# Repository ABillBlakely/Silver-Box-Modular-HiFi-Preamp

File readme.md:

# Silver Box Modular HiFi Preamp

> __Note: This project is still very early in development. Features, functions, and interfaces are subject to change.__

The Silver Box Modular HiFi Preamp allows a person to choose the exact inputs and outputs that a user wants to have. It is common to need to combine or switch between many different sources which all need to go to a single playback source. For instance a person may have TOSLINK optical from their TV, RCA source from a turntable, and a balanced source from a USB audio interface. With this device, all of those can be accommodated and output to one set of speakers.

The chassis provides the analog signal routing, volume control, switching and indication. It is driven by an ESP32 so that functions can be controlled over WiFi, and eventually with smart home integration.

Peripherals are modular cards that can be slotted in to any of the available channels. Peripherals can be active or passive and can function as inputs, outputs, effects, visualizations, maybe more!

The chassis provides each peripheral with:

- Audio send to summing bus, main bus audio output, and audio out from left-adjacent module.
- Global mute and per peripheral muting.
- +/- 12V, +5V, +3.3V power rails.
- An I2C data interface with interrupt capabilities.
- Automatic identification of common module types with additional configuration possible over I2C.

# Current Status

__April 25 2023 Update:__ The project is currently in the __hardware prototyping__ phase. PCB's have been produced and are being assembled. Very close to beginning testing. A minimum viable product could be functional by end of May 2023.

Design files will be updated here as progress is made.

The current schematics are available in .pdf in the __ecad__ folder:

- [ecad/motherboard.pdf](ecad/motherboard.pdf)
- [ecad/controlboard.pdf](ecad/controlboard.pdf)
- [ecad/peripheral-example-board.pdf](ecad/peripheral-example-board.pdf)
- [ecad/prototype-power-supply.pdf](ecad/prototype-power-supply.pdf)

The current 3D models/assemblies for the project are available in .step format in the __mcad__ folder:

- [mcad/silver-box-modular_assembly.step](mcad/silver-box-modular_assembly.step)
- [mcad/motherboard.step](mcad/motherboard.step)
- [mcad/controlboard.step](mcad/controlboard.step)
- [mcad/peripheral-example-board.step](mcad/peripheral-example-board.step)

The BOM for this project is evolving and changing with the project. The current state of the BOM can be viewed at 

- [Motherboard](https://octopart.com/bom-tool/XiIWqOJY)
- [Peripheral test board](https://octopart.com/bom-tool/2ID8Y56N)
- [Protype power supply](https://octopart.com/bom-tool/b4PDtAU9)

Next steps:

- [ ] Bring docs up to date with current development state.
- [ ] Setup dev environment
- [ ] Document the mcad model and explain key features.
- [ ] Organize and refine the 3d prints that will be required for the prototype.
- [ ] Put together power supply module that will be used for early development.
  	- Board should have breakouts for external lab power option
  	- MCU for development and testing of I2C, power sequencing, power monitoring
  	- Polyfuse or other protection circuit. 
- [x] Create blank/passive modules for prototyping.
- [x] Synchronize/clean the Octopart BOM with the schematic.
- [x] Final review and production of prototype PCB's.

Farther out:

- 4 layer board after hardware features and form is frozen.
- Power supply design following findings learned from prototyping efforts.
- Expand available peripheral designs, active balanced I/O. Headphone amp output, S/PDIF digital input, VU 
- Integrate with MQTT for smart home capabilities. Eventual integration with commercial smart home systems.

# Concept sketches/renders:

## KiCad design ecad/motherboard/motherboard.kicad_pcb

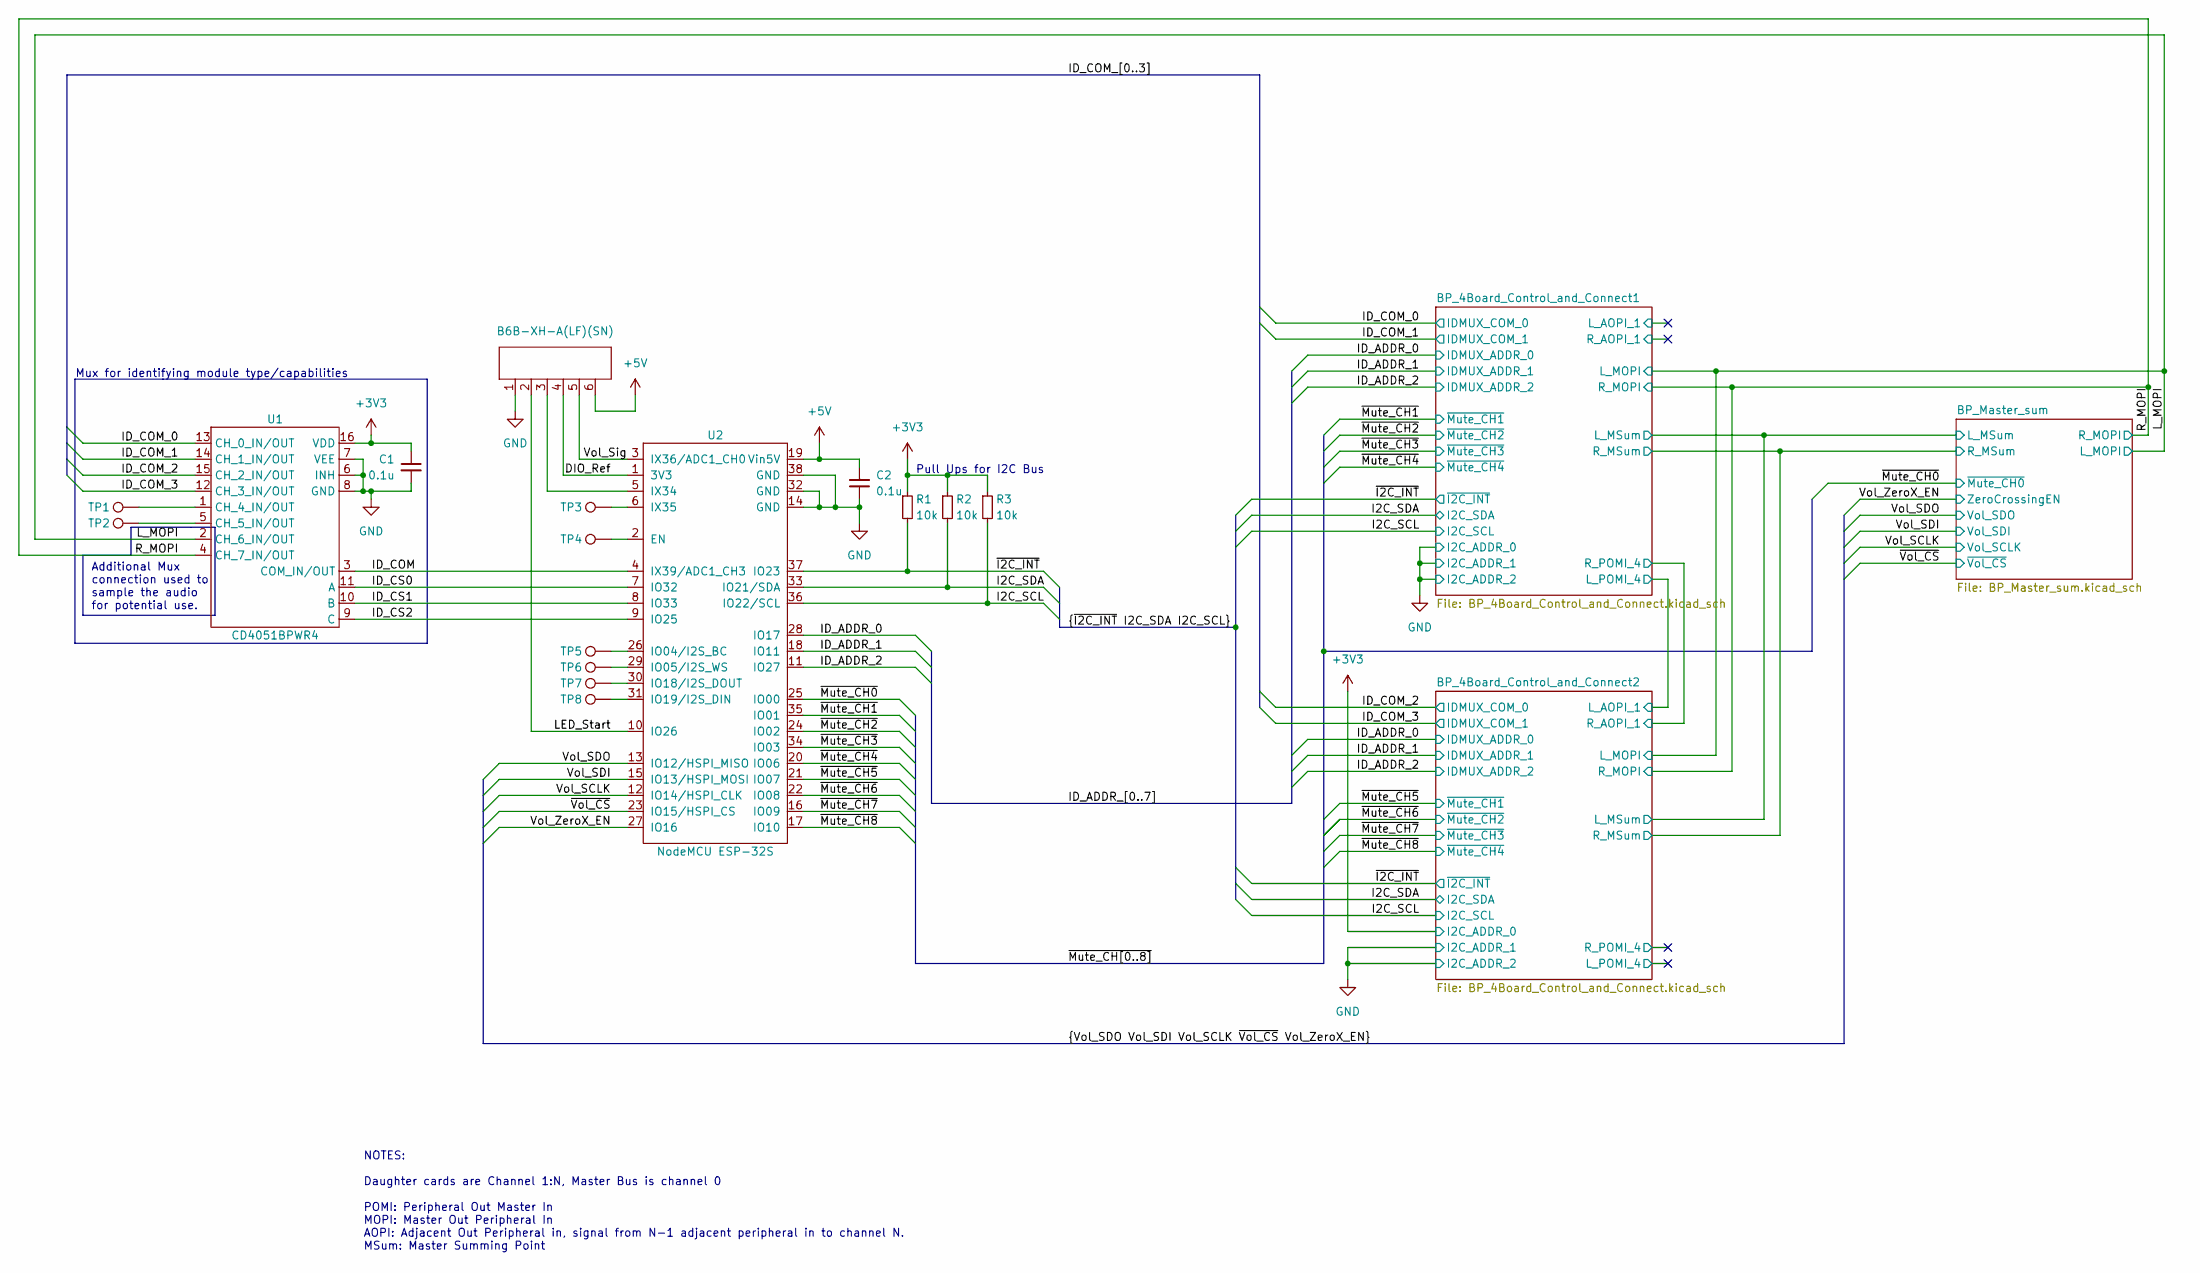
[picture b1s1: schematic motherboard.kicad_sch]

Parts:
C1, C2: 0.1u; C_0603_1608Metric_Pad1.08x0.95mm_HandSolder; MPN C0603C104M5RACTU
J1: B6B-XH-A(LF)(SN); MPN B6B-XH-A(LF)(SN)
R1, R2, R3: 10k; R_0603_1608Metric_Pad0.98x0.95mm_HandSolder; MPN RC0603JR-1010KL
TP1, TP2, TP3, TP4, TP5, TP6, TP7, TP8: TestPoint; TestPoint_Pad_D3.0mm
U1: CD4051BPWR4; CD4051BPWR; MPN CD4051BPWR
U2: NodeMCU ESP-32S

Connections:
+3V3: C1.1, R1.1, R2.1, R3.1, U1.16 (VDD); also elsewhere on the board
+5V: C2.2, J1.6, U2.19 (Vin5V); also elsewhere on the board
/DIO_Ref: J1.4, U2.1 (3V3)
/I2C_SCL: R3.2, U2.36 (IO22/SCL); also elsewhere on the board
/I2C_SDA: R2.2, U2.33 (IO21/SDA); also elsewhere on the board
/ID_ADDR_0: U2.28 (IO17); also elsewhere on the board
/ID_ADDR_1: U2.18 (IO11); also elsewhere on the board
/ID_ADDR_2: U2.11 (IO27); also elsewhere on the board
/ID_COM: U1.3 (COM_IN/OUT), U2.4 (IX39/ADC1_CH3)
/ID_COM_0: U1.13 (CH_0_IN/OUT); also elsewhere on the board
/ID_COM_1: U1.14 (CH_1_IN/OUT); also elsewhere on the board
/ID_COM_2: U1.15 (CH_2_IN/OUT); also elsewhere on the board
/ID_COM_3: U1.12 (CH_3_IN/OUT); also elsewhere on the board
/ID_CS0: U1.11 (A), U2.7 (IO32)
/ID_CS1: U1.10 (B), U2.8 (IO33)
/ID_CS2: U1.9 (C), U2.9 (IO25)
/LED_Start: J1.2, U2.10 (IO26)
/L_MOPI: U1.2 (CH_6_IN/OUT); also elsewhere on the board
/R_MOPI: U1.4 (CH_7_IN/OUT); also elsewhere on the board
/Vol_SCLK: U2.12 (IO14/HSPI_CLK); also elsewhere on the board
/Vol_SDI: U2.15 (IO13/HSPI_MOSI); also elsewhere on the board
/Vol_SDO: U2.13 (IO12/HSPI_MISO); also elsewhere on the board
/Vol_Sig: J1.5, U2.3 (IX36/ADC1_CH0)
/Vol_ZeroX_EN: U2.27 (IO16); also elsewhere on the board
/~I2C_INT: R1.2, U2.37 (IO23); also elsewhere on the board
/~Mute_CH0: U2.25 (IO00); also elsewhere on the board
/~Mute_CH1: U2.35 (IO01); also elsewhere on the board
/~Mute_CH2: U2.24 (IO02); also elsewhere on the board
/~Mute_CH3: U2.34 (IO03); also elsewhere on the board
/~Mute_CH4: U2.20 (IO06); also elsewhere on the board
/~Mute_CH5: U2.21 (IO07); also elsewhere on the board
/~Mute_CH6: U2.22 (IO08); also elsewhere on the board
/~Mute_CH7: U2.16 (IO09); also elsewhere on the board
/~Mute_CH8: U2.17 (IO10); also elsewhere on the board
/~Vol_CS: U2.23 (IO15/HSPI_CS); also elsewhere on the board
GND: C1.2, C2.1, J1.1, U1.6 (INH), U1.7 (VEE), U1.8 (GND), U2.14 (GND), U2.32 (GND), U2.38 (GND); also elsewhere on the board
unnamed: TP1.1, U1.1 (CH_4_IN/OUT)
unnamed: TP2.1, U1.5 (CH_5_IN/OUT)
unnamed: TP4.1, U2.2 (EN)
unnamed: TP5.1, U2.26 (IO04/I2S_BC)
unnamed: TP6.1, U2.29 (IO05/I2S_WS)
unnamed: TP7.1, U2.30 (IO18/I2S_DOUT)
unnamed: TP8.1, U2.31 (IO19/I2S_DIN)
unnamed: J1.3, U2.5 (IX34)
unnamed: TP3.1, U2.6 (IX35)

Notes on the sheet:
Pull Ups for I2C Bus
NOTES: Daughter cards are Channel 1:N, Master Bus is channel 0 POMI: Peripheral Out Master In MOPI: Master Out Peripheral In AOPI: Adjacent Out Peripheral in, signal from N-1 adjacent peripheral in to channel N. MSum: Master Summing Point
Mux for identifying module type/capabilities
Additional Mux connection used to sample the audio for potential use.

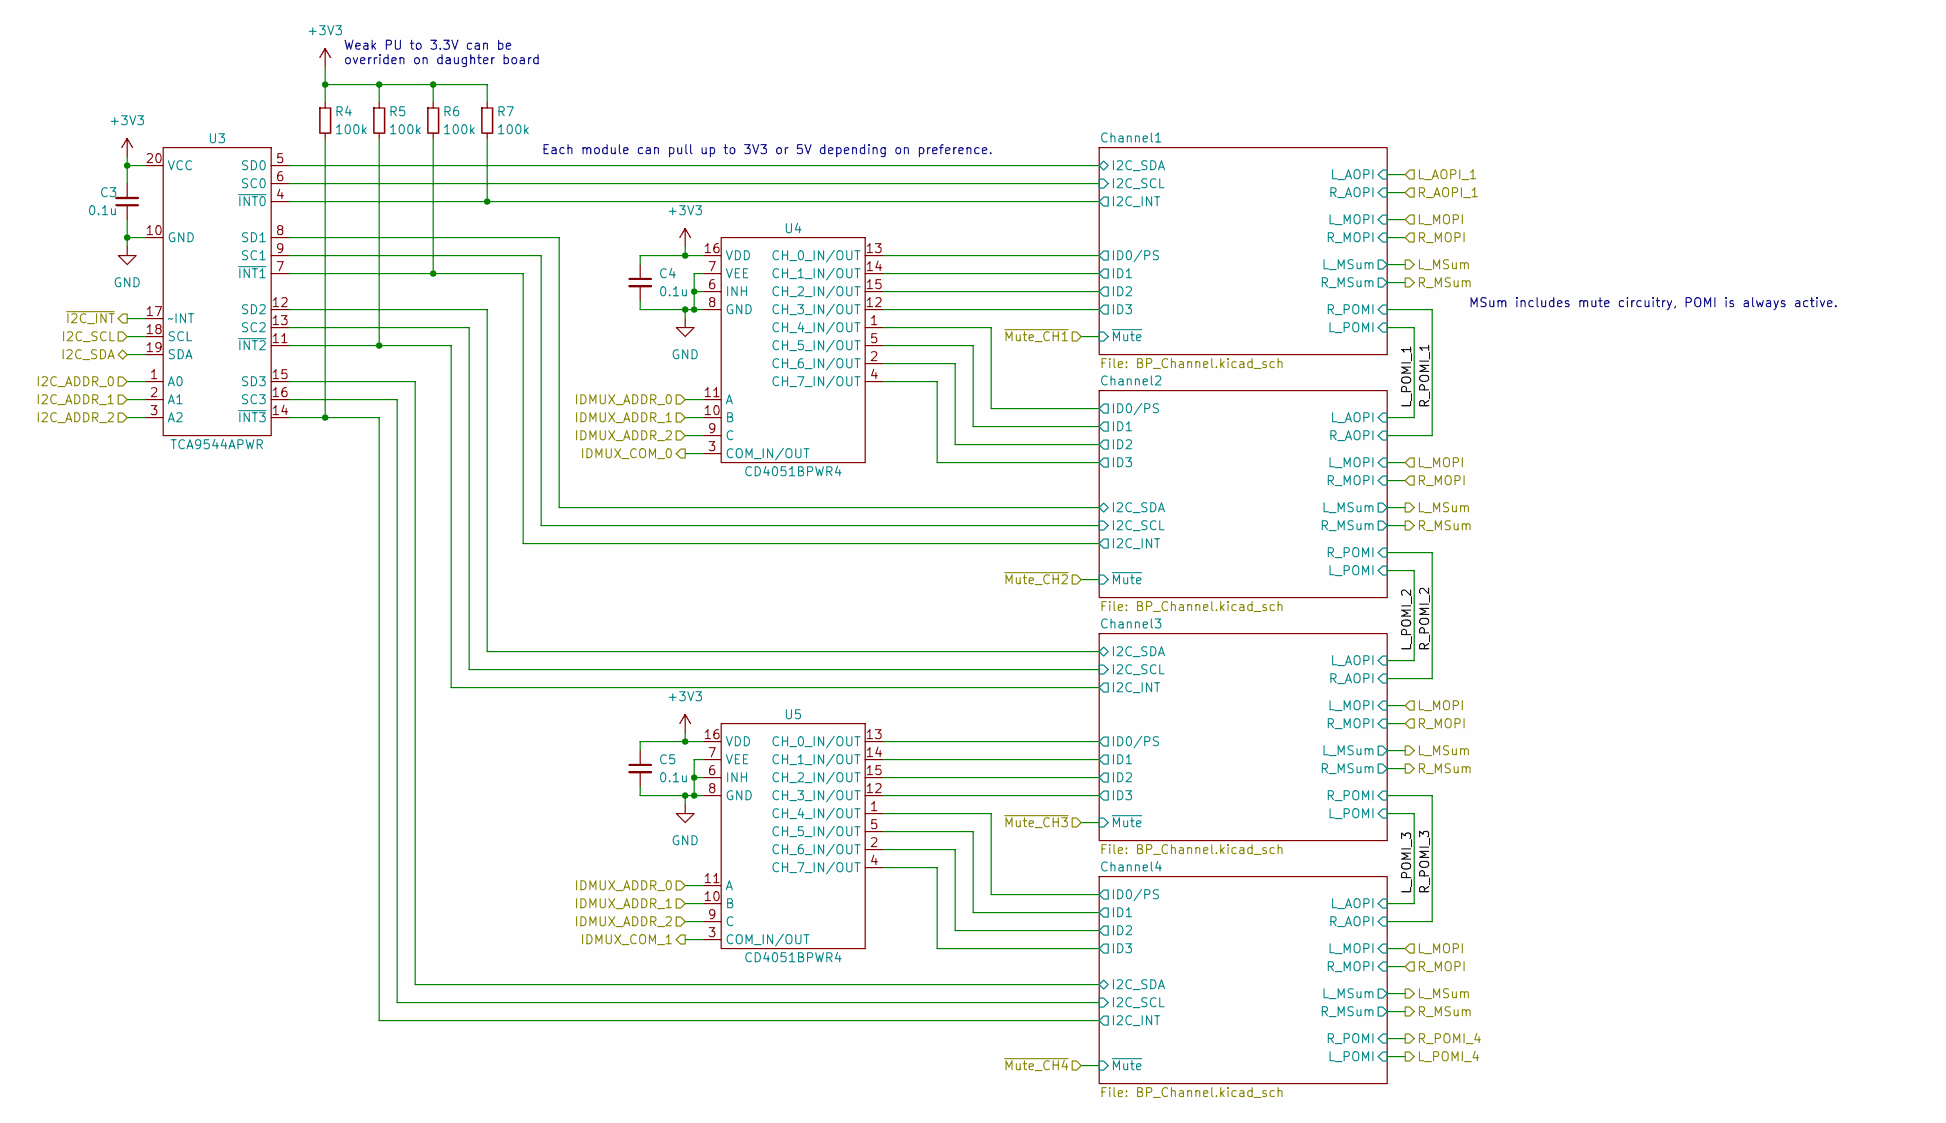
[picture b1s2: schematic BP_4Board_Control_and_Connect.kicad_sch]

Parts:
C3, C4, C5: 0.1u; C_0603_1608Metric_Pad1.08x0.95mm_HandSolder; MPN C0603C104M5RACTU
R4, R5, R6, R7: 100k; R_0603_1608Metric_Pad0.98x0.95mm_HandSolder; MPN C0603FR-07100KL
U3: TCA9544APWR; TCA9544AAPWR; MPN TCA9544APWR
U4, U5: CD4051BPWR4; CD4051BPWR; MPN CD4051BPWR

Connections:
+3V3: C3.2, C4.1, C5.1, R4.1, R5.1, R6.1, R7.1, U3.20 (VCC), U4.16 (VDD), U5.16 (VDD); also elsewhere on the board
/BP_4Board_Control_and_Connect1/Channel1/I2C_INT: R7.2, U3.4 (~INT0); also elsewhere on the board
/BP_4Board_Control_and_Connect1/Channel1/I2C_SCL: U3.6 (SC0); also elsewhere on the board
/BP_4Board_Control_and_Connect1/Channel1/I2C_SDA: U3.5 (SD0); also elsewhere on the board
/BP_4Board_Control_and_Connect1/Channel1/ID0/PS: U4.13 (CH_0_IN/OUT); also elsewhere on the board
/BP_4Board_Control_and_Connect1/Channel1/ID1: U4.14 (CH_1_IN/OUT); also elsewhere on the board
/BP_4Board_Control_and_Connect1/Channel1/ID2: U4.15 (CH_2_IN/OUT); also elsewhere on the board
/BP_4Board_Control_and_Connect1/Channel1/ID3: U4.12 (CH_3_IN/OUT); also elsewhere on the board
/BP_4Board_Control_and_Connect1/Channel2/I2C_INT: R6.2, U3.7 (~INT1); also elsewhere on the board
/BP_4Board_Control_and_Connect1/Channel2/I2C_SCL: U3.9 (SC1); also elsewhere on the board
/BP_4Board_Control_and_Connect1/Channel2/I2C_SDA: U3.8 (SD1); also elsewhere on the board
/BP_4Board_Control_and_Connect1/Channel2/ID0/PS: U4.1 (CH_4_IN/OUT); also elsewhere on the board
/BP_4Board_Control_and_Connect1/Channel2/ID1: U4.5 (CH_5_IN/OUT); also elsewhere on the board
/BP_4Board_Control_and_Connect1/Channel2/ID2: U4.2 (CH_6_IN/OUT); also elsewhere on the board
/BP_4Board_Control_and_Connect1/Channel2/ID3: U4.4 (CH_7_IN/OUT); also elsewhere on the board
/BP_4Board_Control_and_Connect1/Channel3/I2C_INT: R5.2, U3.11 (~INT2); also elsewhere on the board
/BP_4Board_Control_and_Connect1/Channel3/I2C_SCL: U3.13 (SC2); also elsewhere on the board
/BP_4Board_Control_and_Connect1/Channel3/I2C_SDA: U3.12 (SD2); also elsewhere on the board
/BP_4Board_Control_and_Connect1/Channel3/ID0/PS: U5.13 (CH_0_IN/OUT); also elsewhere on the board
/BP_4Board_Control_and_Connect1/Channel3/ID1: U5.14 (CH_1_IN/OUT); also elsewhere on the board
/BP_4Board_Control_and_Connect1/Channel3/ID2: U5.15 (CH_2_IN/OUT); also elsewhere on the board
/BP_4Board_Control_and_Connect1/Channel3/ID3: U5.12 (CH_3_IN/OUT); also elsewhere on the board
/BP_4Board_Control_and_Connect1/Channel4/I2C_INT: R4.2, U3.14 (~INT3); also elsewhere on the board
/BP_4Board_Control_and_Connect1/Channel4/I2C_SCL: U3.16 (SC3); also elsewhere on the board
/BP_4Board_Control_and_Connect1/Channel4/I2C_SDA: U3.15 (SD3); also elsewhere on the board
/BP_4Board_Control_and_Connect1/Channel4/ID0/PS: U5.1 (CH_4_IN/OUT); also elsewhere on the board
/BP_4Board_Control_and_Connect1/Channel4/ID1: U5.5 (CH_5_IN/OUT); also elsewhere on the board
/BP_4Board_Control_and_Connect1/Channel4/ID2: U5.2 (CH_6_IN/OUT); also elsewhere on the board
/BP_4Board_Control_and_Connect1/Channel4/ID3: U5.4 (CH_7_IN/OUT); also elsewhere on the board
/I2C_SCL: U3.18 (SCL); also elsewhere on the board
/I2C_SDA: U3.19 (SDA); also elsewhere on the board
/ID_ADDR_0: U4.11 (A), U5.11 (A); also elsewhere on the board
/ID_ADDR_1: U4.10 (B), U5.10 (B); also elsewhere on the board
/ID_ADDR_2: U4.9 (C), U5.9 (C); also elsewhere on the board
/ID_COM_0: U4.3 (COM_IN/OUT); also elsewhere on the board
/ID_COM_1: U5.3 (COM_IN/OUT); also elsewhere on the board
/~I2C_INT: U3.17 (~INT); also elsewhere on the board
GND: C3.1, C4.2, C5.2, U3.1 (A0), U3.2 (A1), U3.3 (A2), U3.10 (GND), U4.6 (INH), U4.7 (VEE), U4.8 (GND), U5.6 (INH), U5.7 (VEE), U5.8 (GND); also elsewhere on the board

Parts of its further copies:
C22, C23, C24: 0.1u; C_0603_1608Metric_Pad1.08x0.95mm_HandSolder; MPN C0603C104M5RACTU
R48, R49, R50, R51: 100k; R_0603_1608Metric_Pad0.98x0.95mm_HandSolder; MPN C0603FR-07100KL
U18: TCA9544APWR; TCA9544AAPWR; MPN TCA9544APWR
U19, U20: CD4051BPWR4; CD4051BPWR; MPN CD4051BPWR

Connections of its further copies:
+3V3: C22.2, C23.1, C24.1, R48.1, R49.1, R50.1, R51.1, U18.1 (A0), U18.20 (VCC), U19.16 (VDD), U20.16 (VDD); also elsewhere on the board
/BP_4Board_Control_and_Connect2/Channel1/I2C_INT: R51.2, U18.4 (~INT0); also elsewhere on the board
/BP_4Board_Control_and_Connect2/Channel1/I2C_SCL: U18.6 (SC0); also elsewhere on the board
/BP_4Board_Control_and_Connect2/Channel1/I2C_SDA: U18.5 (SD0); also elsewhere on the board
/BP_4Board_Control_and_Connect2/Channel1/ID0/PS: U19.13 (CH_0_IN/OUT); also elsewhere on the board
/BP_4Board_Control_and_Connect2/Channel1/ID1: U19.14 (CH_1_IN/OUT); also elsewhere on the board
/BP_4Board_Control_and_Connect2/Channel1/ID2: U19.15 (CH_2_IN/OUT); also elsewhere on the board
/BP_4Board_Control_and_Connect2/Channel1/ID3: U19.12 (CH_3_IN/OUT); also elsewhere on the board
/BP_4Board_Control_and_Connect2/Channel2/I2C_INT: R50.2, U18.7 (~INT1); also elsewhere on the board
/BP_4Board_Control_and_Connect2/Channel2/I2C_SCL: U18.9 (SC1); also elsewhere on the board
/BP_4Board_Control_and_Connect2/Channel2/I2C_SDA: U18.8 (SD1); also elsewhere on the board
/BP_4Board_Control_and_Connect2/Channel2/ID0/PS: U19.1 (CH_4_IN/OUT); also elsewhere on the board
/BP_4Board_Control_and_Connect2/Channel2/ID1: U19.5 (CH_5_IN/OUT); also elsewhere on the board
/BP_4Board_Control_and_Connect2/Channel2/ID2: U19.2 (CH_6_IN/OUT); also elsewhere on the board
/BP_4Board_Control_and_Connect2/Channel2/ID3: U19.4 (CH_7_IN/OUT); also elsewhere on the board
/BP_4Board_Control_and_Connect2/Channel3/I2C_INT: R49.2, U18.11 (~INT2); also elsewhere on the board
/BP_4Board_Control_and_Connect2/Channel3/I2C_SCL: U18.13 (SC2); also elsewhere on the board
/BP_4Board_Control_and_Connect2/Channel3/I2C_SDA: U18.12 (SD2); also elsewhere on the board
/BP_4Board_Control_and_Connect2/Channel3/ID0/PS: U20.13 (CH_0_IN/OUT); also elsewhere on the board
/BP_4Board_Control_and_Connect2/Channel3/ID1: U20.14 (CH_1_IN/OUT); also elsewhere on the board
/BP_4Board_Control_and_Connect2/Channel3/ID2: U20.15 (CH_2_IN/OUT); also elsewhere on the board
/BP_4Board_Control_and_Connect2/Channel3/ID3: U20.12 (CH_3_IN/OUT); also elsewhere on the board
/BP_4Board_Control_and_Connect2/Channel4/I2C_INT: R48.2, U18.14 (~INT3); also elsewhere on the board
/BP_4Board_Control_and_Connect2/Channel4/I2C_SCL: U18.16 (SC3); also elsewhere on the board
/BP_4Board_Control_and_Connect2/Channel4/I2C_SDA: U18.15 (SD3); also elsewhere on the board
/BP_4Board_Control_and_Connect2/Channel4/ID0/PS: U20.1 (CH_4_IN/OUT); also elsewhere on the board
/BP_4Board_Control_and_Connect2/Channel4/ID1: U20.5 (CH_5_IN/OUT); also elsewhere on the board
/BP_4Board_Control_and_Connect2/Channel4/ID2: U20.2 (CH_6_IN/OUT); also elsewhere on the board
/BP_4Board_Control_and_Connect2/Channel4/ID3: U20.4 (CH_7_IN/OUT); also elsewhere on the board
/I2C_SCL: U18.18 (SCL); also elsewhere on the board
/I2C_SDA: U18.19 (SDA); also elsewhere on the board
/ID_ADDR_0: U19.11 (A), U20.11 (A); also elsewhere on the board
/ID_ADDR_1: U19.10 (B), U20.10 (B); also elsewhere on the board
/ID_ADDR_2: U19.9 (C), U20.9 (C); also elsewhere on the board
/ID_COM_2: U19.3 (COM_IN/OUT); also elsewhere on the board
/ID_COM_3: U20.3 (COM_IN/OUT); also elsewhere on the board
/~I2C_INT: U18.17 (~INT); also elsewhere on the board
GND: C22.1, C23.2, C24.2, U18.2 (A1), U18.3 (A2), U18.10 (GND), U19.6 (INH), U19.7 (VEE), U19.8 (GND), U20.6 (INH), U20.7 (VEE), U20.8 (GND); also elsewhere on the board

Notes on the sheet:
MSum includes mute circuitry, POMI is always active.
Weak PU to 3.3V can be overriden on daughter board
Each module can pull up to 3V3 or 5V depending on preference.

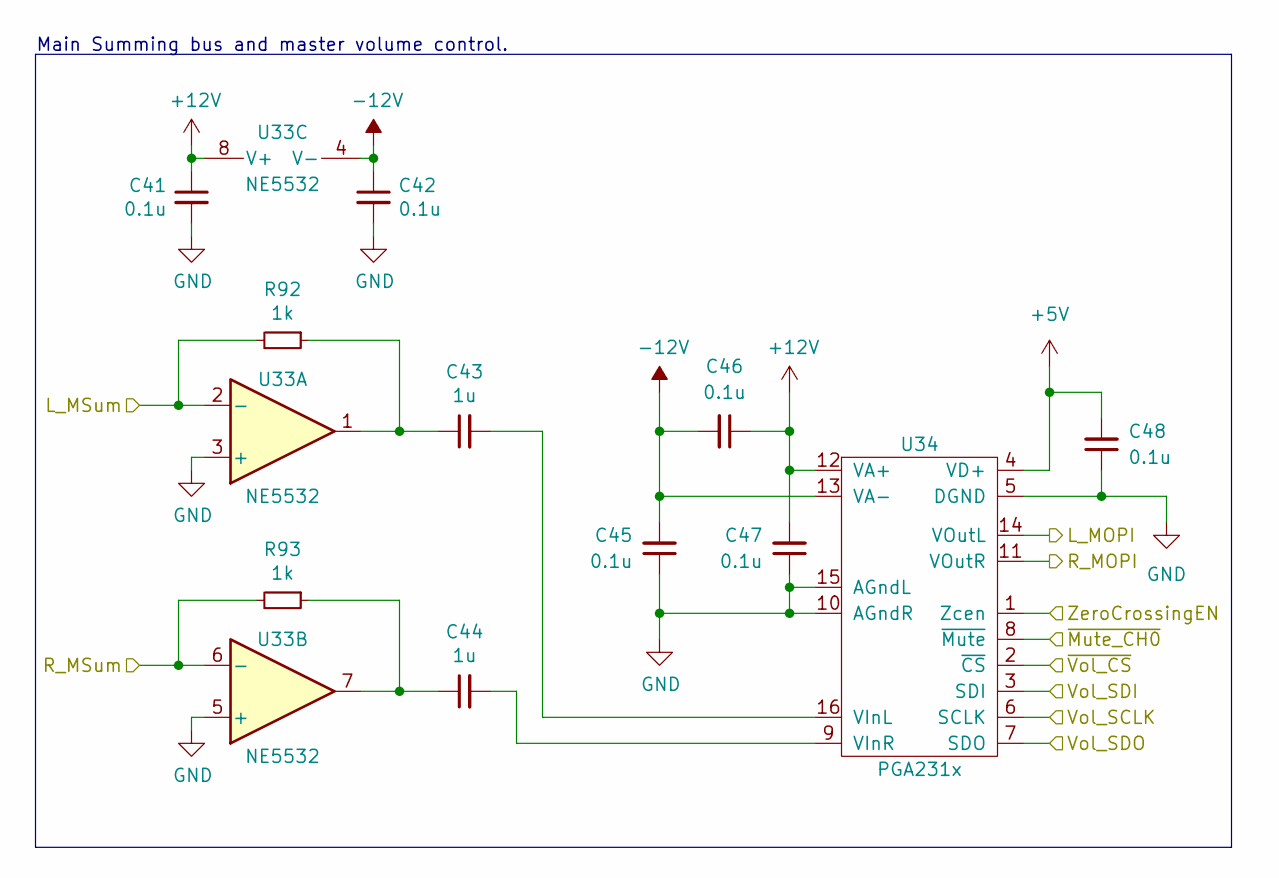
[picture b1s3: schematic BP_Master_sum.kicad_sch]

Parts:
C41, C42, C45, C46, C47, C48: 0.1u; C_0603_1608Metric_Pad1.08x0.95mm_HandSolder; MPN C0603C104M5RACTU
C43, C44: 1u; C_2220_5650Metric_Pad1.97x5.40mm_HandSolder; MPN GRM55DR72E105KW01L
R92, R93: 1k; R_0603_1608Metric_Pad0.98x0.95mm_HandSolder; MPN RT0603FRE071KL
U33: NE5532; NE5532 SOIC8; MPN NE5532ADR
U34: PGA231x; PGA231XU; MPN PGA2310UA/1K

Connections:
+5V: C48.2, U34.4 (VD+); also elsewhere on the board
+12V: C41.1, C46.1, C47.2, U33.8 (V+), U34.12 (VA+); also elsewhere on the board
-12V: C42.1, C45.2, C46.2, U33.4 (V-), U34.13 (VA-); also elsewhere on the board
/BP_4Board_Control_and_Connect1/L_MSum: R92.2, U33.2 (-); also elsewhere on the board
/BP_4Board_Control_and_Connect1/R_MSum: R93.2, U33.6 (-); also elsewhere on the board
/L_MOPI: U34.14 (VOutL); also elsewhere on the board
/R_MOPI: U34.11 (VOutR); also elsewhere on the board
/Vol_SCLK: U34.6 (SCLK); also elsewhere on the board
/Vol_SDI: U34.3 (SDI); also elsewhere on the board
/Vol_SDO: U34.7 (SDO); also elsewhere on the board
/Vol_ZeroX_EN: U34.1 (Zcen); also elsewhere on the board
/~Mute_CH0: U34.8 (~Mute); also elsewhere on the board
/~Vol_CS: U34.2 (~CS); also elsewhere on the board
GND: C41.2, C42.2, C45.1, C47.1, C48.1, U33.3 (+), U33.5 (+), U34.5 (DGND), U34.10 (AGndR), U34.15 (AGndL); also elsewhere on the board
unnamed: C43.1, R92.1, U33.1
unnamed: C44.1, R93.1, U33.7
unnamed: C43.2, U34.16 (VInL)
unnamed: C44.2, U34.9 (VInR)

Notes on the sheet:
Main Summing bus and master volume control.

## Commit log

2023-02-01 Add 3d models for some IC parts
2023-02-01 Huge overhaul of whole project, nearly ready for PCB prototype layout.
2023-02-01 Remove kicad autobackups from git
2023-02-02 Add readme and concept sketch montage.
2023-02-02 Update to Kicad 7 and generate PDF schematic.
2023-02-02 Add link to pdf schematic.
2023-02-03 More 3d Models and small fixes to footprints.
2023-02-03 Fixes to footprint numbering in multi-unit parts.
2023-02-03 Begin rough PCB layout.
2023-02-09 Small fixes/improvements to relay IC 3d models.
2023-02-09 Layout signal conditioning portion with approximate traces, update status and next steps in readme.
2023-03-16 Continue board layout, partial power and digital signals are laid.
2023-03-17 2023.03.17 I2C out to master is current sticking point. Also needs review of grounds.
2023-03-18 Route mutes and i2c master, rough positioning of esp32, will likely move towards a corner later.
2023-03-27 Remove unnecessary annular ring on NPTH.
2023-03-27 Route all traces, needs review. Still needs silkscreen cleanup and conversion to true two board file.
2023-03-28 Change mechanical pad to polyline to avoid drc complaint with through hole.
2023-03-28 Center footprint anchor point of switch
2023-03-28 Full layout for review after checking mechanical assembly.
2023-03-28 Separate the board files and export .step so that the mechanical assembly can be reviewed.
2023-03-28 Revise next steps as first round of pcb design wraps up.
2023-03-30 Split into truly multiboard preoject to simplify* organization (*Hopefully!)
2023-03-30 Add new peripheral example board to better determine peripheral envelope and orientation in 3d space. Add several new parts to symbols, footprints, and 3dmodels
2023-03-31 Small changes and cleanup as 3dmodels are pieced together.
2023-03-31 Fixes for manufacturer models that had geometry errors in onshape.
2023-03-31 Change addressable LED to new part that is still available.
2023-04-02 Good state for mechanical assembly, can bounce back to pcb review now that board outlines are close.
2023-04-06 Fix 3d models getting duplicated output in .step export
2023-04-10 Small tweaks to routing for better signal return paths. Fix minor footprint issues: missing courtyards, smt parts labeled as through hole.
2023-04-11 Add billtech logo footprint.
2023-04-11 Add silkscreen markings.
2023-04-25 Updates and additions for peripheral test board and power supply prototype
2023-04-25 Add manufacturer part numbers into Kicad Schematics
2023-04-25 Version 0.1 of the peripheral example board sent to PCB manufaturer.
2023-04-25 First start of Functional description
2023-04-25 Add 3d model of bulk power cap.
2023-04-25 Add symbols for prototype power board
2023-04-25 Begin design of protype power supply.
2023-04-25 Update schematic pdf and PCBA .step files
2023-04-25 update current status and organization of project.
2023-04-27 Fix missing mask and paste layers on support pad of PCI connector. Open mask expansion slightly and close paste slightly.
2023-05-01 Update Net labels for better consistency.
2023-05-01 Platform independent mute_driver with unit tests.
2023-05-01 Begin Error handling with test mock.
2023-05-01 Begin unit tests and driver for PGA231X volume control.
2023-05-01 Initialize base idMuxDriver files.
2023-05-01 Hardware target initial file for build chain test.
